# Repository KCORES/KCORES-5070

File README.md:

# DELL Wyse 5070 Hacking

关于 DELL Wyse 5070 主板的一些硬件分析和逆向工程

- 介绍视频：[省到离谱，比树莓派还省电的x86主板](https://youtu.be/9opQ4gsh4Hg)

- 交流QQ群：[655944532](https://jq.qq.com/?_wv=1027&k=KV0wy6gJ)

## 主要贡献者

- [@Havoc](https://github.com/Wangrb)
- [@Naivekun](https://github.com/naivekun)
- [@AlphaArea](https://github.com/alphaarea)

## Wyse 5070 基本介绍

Wyse 5070 分为胖瘦两种机型, 主要区别如下

| 瘦机          |   胖机            |
| ------------- | ----------------- |
| PCIe 插槽空焊 | 有 PCIe 插槽      |
| 无风扇        | 有风扇            |
| 检测 90W 电源 | 检测 120W 电源     |

注: 不同批次的主板, 元器件型号可能存在区别

## 刷 BIOS

BIOS 文件在 BIOS 文件夹中, 刷入可以直接解决电源识别问题并提升性能, 但是 DELL 的保护不允许软刷入 BIOS, 必须使用 CH341A 编程器直接刷入 BIOS 芯片.

BIOS 文件由 [@Naivekun](https://github.com/naivekun) 修改, 主要功能:

- 删除电源功率检测, 只要插上电就能用
- 提高 PL1 睿频限制, 性能看齐 J5040
- 提高 CPU 主频 (未生效)

⚠注意: 刷入 BIOS 可能导致主板序列号和集成网卡 MAC 地址改变

## 电源

### 电压范围

实测 Wyse5070 允许 9~20V 范围的宽电压供电, 如果使用电池可以 4S 锂电池直通, 免去稳压提高电池利用率

### 电源识别

建议使用 DELL 供电转接头, 并且最好买标明已刷入 120W 信息的型号, 免得插到胖机主板上识别为供电不足禁止睿频

不建议使用原装 19V 笔记本电源, 因为后续使用 PCIe 转接卡需要 12V 供电

## 开机排线

开机排线必须连接检测针, 否则开机必跳警告

插座型号: 2.0mm 排针

## 喇叭排线

如果不使用声卡也不使用板载喇叭, 可以不管

插座型号: SH1.25

## eMMC

理论上 eMMC 是标准接口全兼容, 但实际上 intel 的 eMMC 一直存在玄学兼容问题, 如需自行安装或扩容建议选择原装同系列的 eMMC

- SKhynix H26M51002KPR
- SanDisk SDINADF4-16G

## PCIe

**⚠警告: 使用 DIY PCIe 转接板必须搭配 12V DC 电源, 使用 19V 笔记本电源将烧毁 PCIe 设备**

1. 胖机可以直接使用转接卡插上 PCIe 设备使用

2. 除非有电动吸锡器等专业工具, 否则不建议用普通装备挑战 DELL 的多层 PCB 过孔灌锡, 很可能彻底损坏 PCIe 插槽焊盘

3. 时钟请求电路见下图  

4. 转接卡图纸见 pcie 文件夹, 使用 KiCAD 编辑. 转接板尺寸为自制亚克力外壳设计, 不兼容原厂机箱.

## 散热片

散热片模型见 heatsink 文件夹

## 亚克力外壳

亚克力文件见 case 文件夹

- 上板与主板固定使用 M3x14mm 铜柱
- 下板与主板固定使用 M3x6mm 铜柱

该尺寸为自制 PCIe 转接板设计, 不兼容原厂 PCIe 扩展板

## 开机注意事项

Wyse 5070 的开机逻辑和常见 DIY 主板不同, 它的自检发生在更换硬件后的第一次上电时(无论是否按下开机按钮). 

建议使用可显示电流的稳压电源测试, 自检持续数十秒后电流会降低到 0.1A 以下, 此时自检完成可以按电源键开机.

若自检持续一分钟以上, 且电流不波动, 一般是内存没有装好.

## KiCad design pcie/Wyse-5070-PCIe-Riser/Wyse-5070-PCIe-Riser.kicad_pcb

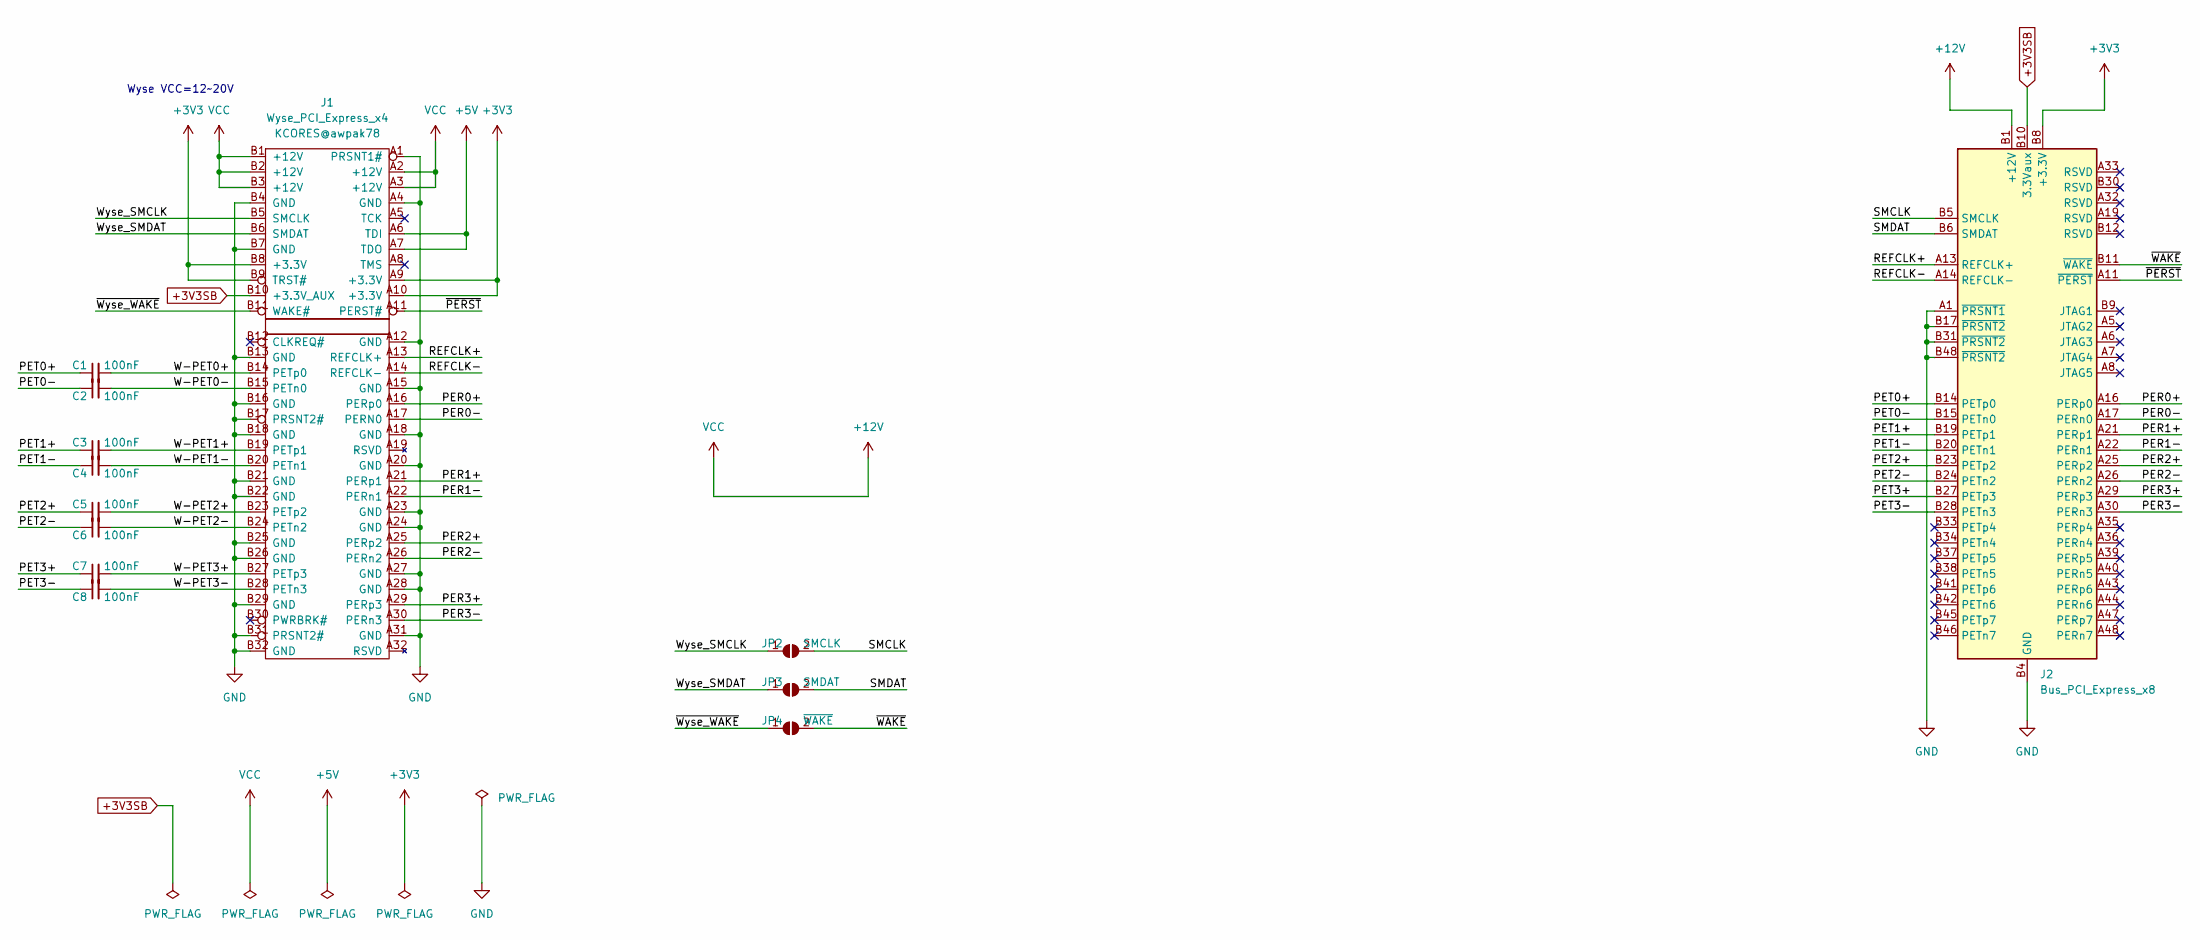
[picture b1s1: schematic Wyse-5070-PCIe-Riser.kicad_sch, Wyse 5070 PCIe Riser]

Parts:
C1, C2, C3, C4, C5, C6, C7, C8: 100nF; C_0402_1005Metric
J1: Wyse_PCI_Express_x4; BUS_PCIexpress_x4
J2: Bus_PCI_Express_x8; PCIe_Vertical_SMT_x8
JP2: SMCLK; SolderJumper-2_P1.3mm_Open_RoundedPad1.0x1.5mm
JP3: SMDAT; SolderJumper-2_P1.3mm_Open_RoundedPad1.0x1.5mm
JP4: ~{WAKE}; SolderJumper-2_P1.3mm_Open_RoundedPad1.0x1.5mm

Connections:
+3V3: J1.A9 (+3.3V), J1.A10 (+3.3V), J1.B8 (+3.3V), J1.B9 (TRST#), J2.A9 (+3.3V), J2.A10 (+3.3V), J2.B8 (+3.3V)
+3V3SB: J1.B10 (+3.3V_AUX), J2.B10 (3.3Vaux)
+5V: J1.A6 (TDI), J1.A7 (TDO)
+12V: J1.A2 (+12V), J1.A3 (+12V), J1.B1 (+12V), J1.B2 (+12V), J1.B3 (+12V), J2.A2 (+12V), J2.A3 (+12V), J2.B1 (+12V), J2.B2 (+12V), J2.B3 (+12V)
/PER0+: J1.A16 (PERp0), J2.A16 (PERp0)
/PER0-: J1.A17 (PERN0), J2.A17 (PERn0)
/PER1+: J1.A21 (PERp1), J2.A21 (PERp1)
/PER1-: J1.A22 (PERn1), J2.A22 (PERn1)
/PER2+: J1.A25 (PERp2), J2.A25 (PERp2)
/PER2-: J1.A26 (PERn2), J2.A26 (PERn2)
/PER3+: J1.A29 (PERp3), J2.A29 (PERp3)
/PER3-: J1.A30 (PERn3), J2.A30 (PERn3)
/PET0+: C1.1, J2.B14 (PETp0)
/PET0-: C2.1, J2.B15 (PETn0)
/PET1+: C3.1, J2.B19 (PETp1)
/PET1-: C4.1, J2.B20 (PETn1)
/PET2+: C5.1, J2.B23 (PETp2)
/PET2-: C6.1, J2.B24 (PETn2)
/PET3+: C7.1, J2.B27 (PETp3)
/PET3-: C8.1, J2.B28 (PETn3)
/REFCLK+: J1.A13 (REFCLK+), J2.A13 (REFCLK+)
/REFCLK-: J1.A14 (REFCLK-), J2.A14 (REFCLK-)
/SMCLK: J2.B5 (SMCLK), JP2.2 (B)
/SMDAT: J2.B6 (SMDAT), JP3.2 (B)
/W-PET0+: C1.2, J1.B14 (PETp0)
/W-PET0-: C2.2, J1.B15 (PETn0)
/W-PET1+: C3.2, J1.B19 (PETp1)
/W-PET1-: C4.2, J1.B20 (PETn1)
/W-PET2+: C5.2, J1.B23 (PETp2)
/W-PET2-: C6.2, J1.B24 (PETn2)
/W-PET3+: C7.2, J1.B27 (PETp3)
/W-PET3-: C8.2, J1.B28 (PETn3)
/Wyse_SMCLK: J1.B5 (SMCLK), JP2.1 (A)
/Wyse_SMDAT: J1.B6 (SMDAT), JP3.1 (A)
/~PERST: J1.A11 (PERST#), J2.A11 (~PERST)
/~WAKE: J2.B11 (~WAKE), JP4.2 (B)
/~Wyse_WAKE: J1.B11 (WAKE#), JP4.1 (A)
GND: J1.A1 (PRSNT1#), J1.A4 (GND), J1.A12 (GND), J1.A15 (GND), J1.A18 (GND), J1.A20 (GND), J1.A23 (GND), J1.A24 (GND), J1.A27 (GND), J1.A28 (GND), J1.A31 (GND), J1.B4 (GND), J1.B7 (GND), J1.B13 (GND), J1.B16 (GND), J1.B17 (PRSNT2#), J1.B18 (GND), J1.B21 (GND), J1.B22 (GND), J1.B25 (GND), J1.B26 (GND), J1.B29 (GND), J1.B31 (PRSNT2#), J1.B32 (GND), J2.A1 (~PRSNT1), J2.A4 (GND), J2.A12 (GND), J2.A15 (GND), J2.A18 (GND), J2.A20 (GND), J2.A23 (GND), J2.A24 (GND), J2.A27 (GND), J2.A28 (GND), J2.A31 (GND), J2.A34 (GND), J2.A37 (GND), J2.A38 (GND), J2.A41 (GND), J2.A42 (GND), J2.A45 (GND), J2.A46 (GND), J2.A49 (GND), J2.B4 (GND), J2.B7 (GND), J2.B13 (GND), J2.B16 (GND), J2.B17 (~PRSNT2), J2.B18 (GND), J2.B21 (GND), J2.B22 (GND), J2.B25 (GND), J2.B26 (GND), J2.B29 (GND), J2.B31 (~PRSNT2), J2.B32 (GND), J2.B35 (GND), J2.B36 (GND), J2.B39 (GND), J2.B40 (GND), J2.B43 (GND), J2.B44 (GND), J2.B47 (GND), J2.B48 (~PRSNT2), J2.B49 (GND)

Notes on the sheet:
Wyse VCC=12~20V

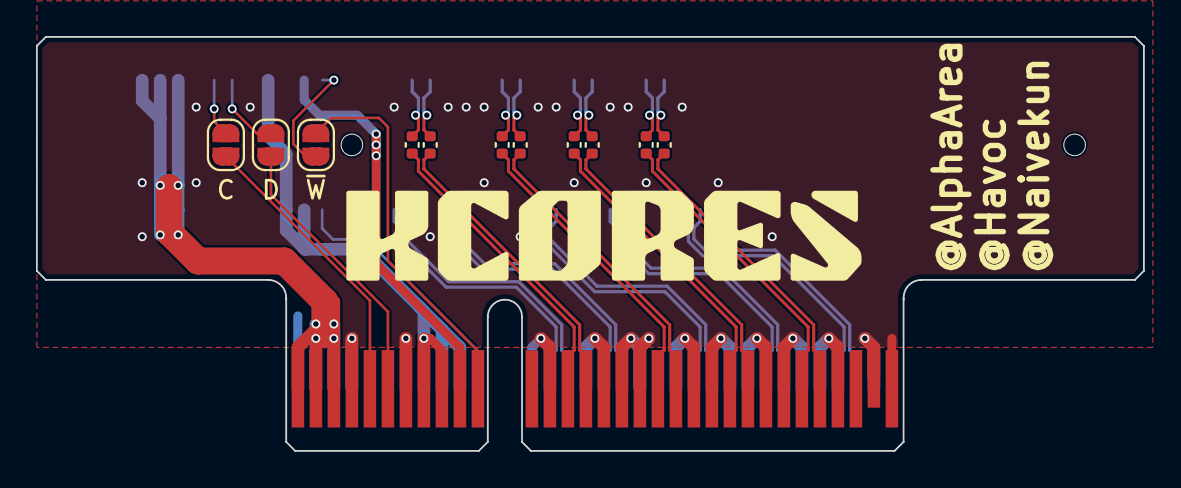
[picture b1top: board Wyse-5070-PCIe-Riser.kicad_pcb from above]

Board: 2 copper layers, 61.5 x 23.0 mm, 13 parts (1 on the bottom side), 38 nets.

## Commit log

2023-03-02 Release
2023-03-02 update link
2023-03-05 update case
